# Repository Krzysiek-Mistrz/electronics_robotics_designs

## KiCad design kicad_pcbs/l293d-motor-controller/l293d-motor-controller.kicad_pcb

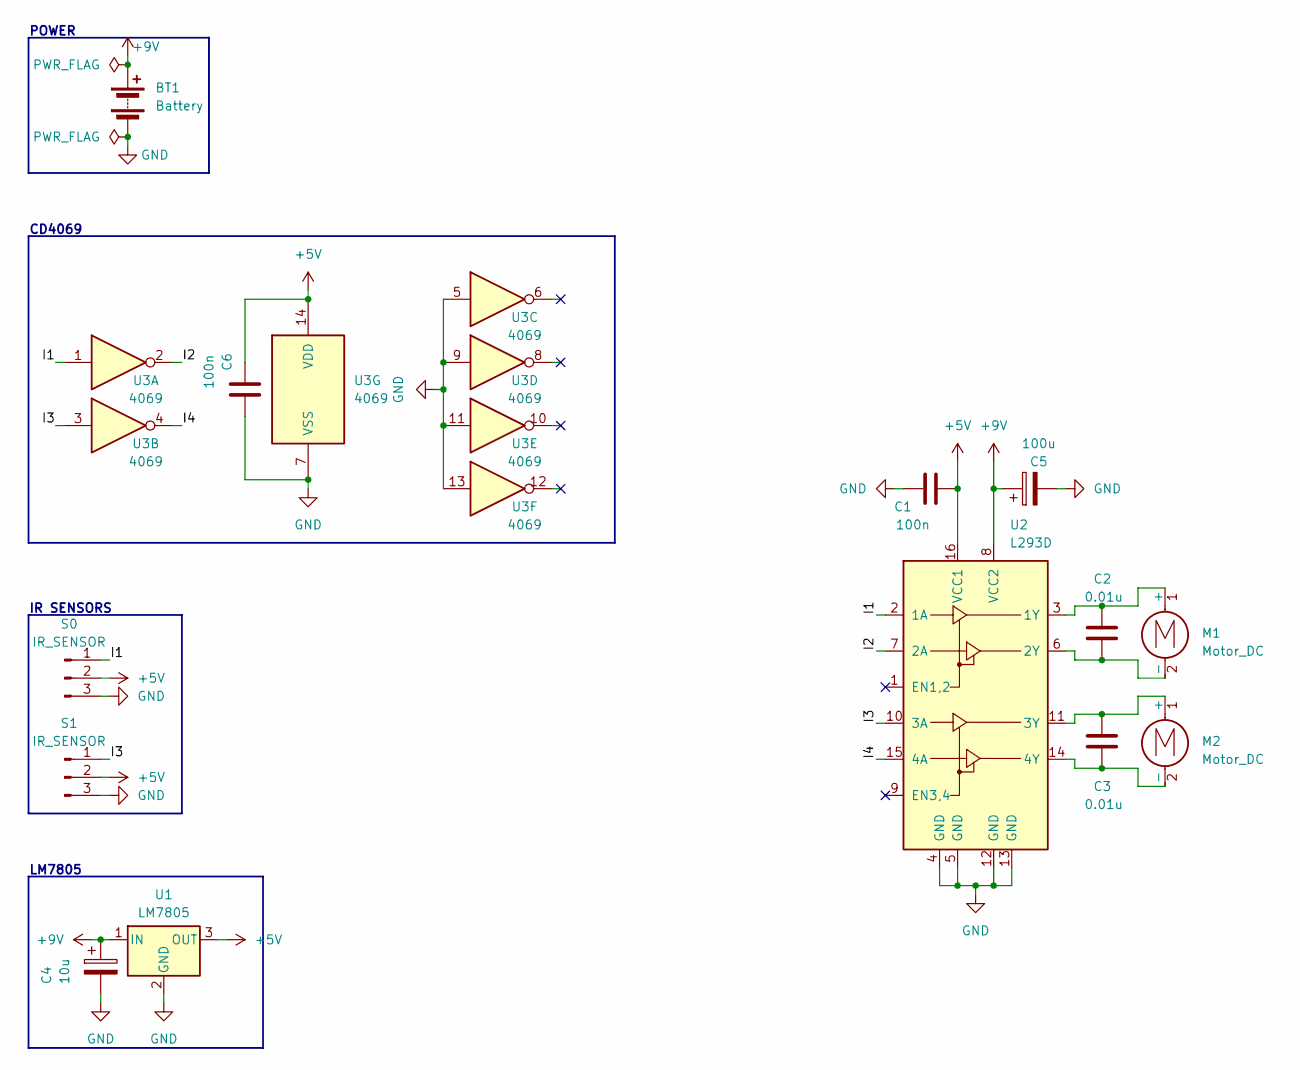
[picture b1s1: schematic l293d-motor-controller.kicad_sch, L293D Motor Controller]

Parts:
BT1: Battery; PinHeader_1x02_P2.54mm_Vertical
C1, C6: 100n; C_Disc_D3.0mm_W1.6mm_P2.50mm
C2, C3: 0.01u; C_Disc_D3.0mm_W1.6mm_P2.50mm
C4: 10u; CP_Radial_D4.0mm_P1.50mm
C5: 100u; CP_Radial_D4.0mm_P1.50mm
M1, M2: Motor_DC; PinHeader_1x02_P2.54mm_Vertical
S0, S1: IR_SENSOR; PinHeader_1x03_P2.54mm_Vertical
U1: LM7805; TO-220-3_Vertical
U2: L293D; DIP-16_W7.62mm
U3: 4069; DIP-14_W7.62mm

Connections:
+5V: C1.2, C6.1, S0.2, S1.2, U1.3 (OUT), U2.16 (VCC1), U3.14 (VDD)
+9V: BT1.1 (+), C4.1, C5.1, U1.1 (IN), U2.8 (VCC2)
/I1: S0.1, U2.2 (1A), U3.1
/I2: U2.7 (2A), U3.2
/I3: S1.1, U2.10 (3A), U3.3
/I4: U2.15 (4A), U3.4
GND: BT1.2 (-), C1.1, C4.2, C5.2, C6.2, S0.3, S1.3, U1.2 (GND), U2.4 (GND), U2.5 (GND), U2.12 (GND), U2.13 (GND), U3.5, U3.7 (VSS), U3.9, U3.11, U3.13
unnamed: C2.1, M1.1 (+), U2.3 (1Y)
unnamed: C2.2, M1.2 (-), U2.6 (2Y)
unnamed: C3.1, M2.1 (+), U2.11 (3Y)
unnamed: C3.2, M2.2 (-), U2.14 (4Y)

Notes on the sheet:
LM7805
POWER
IR SENSORS
CD4069

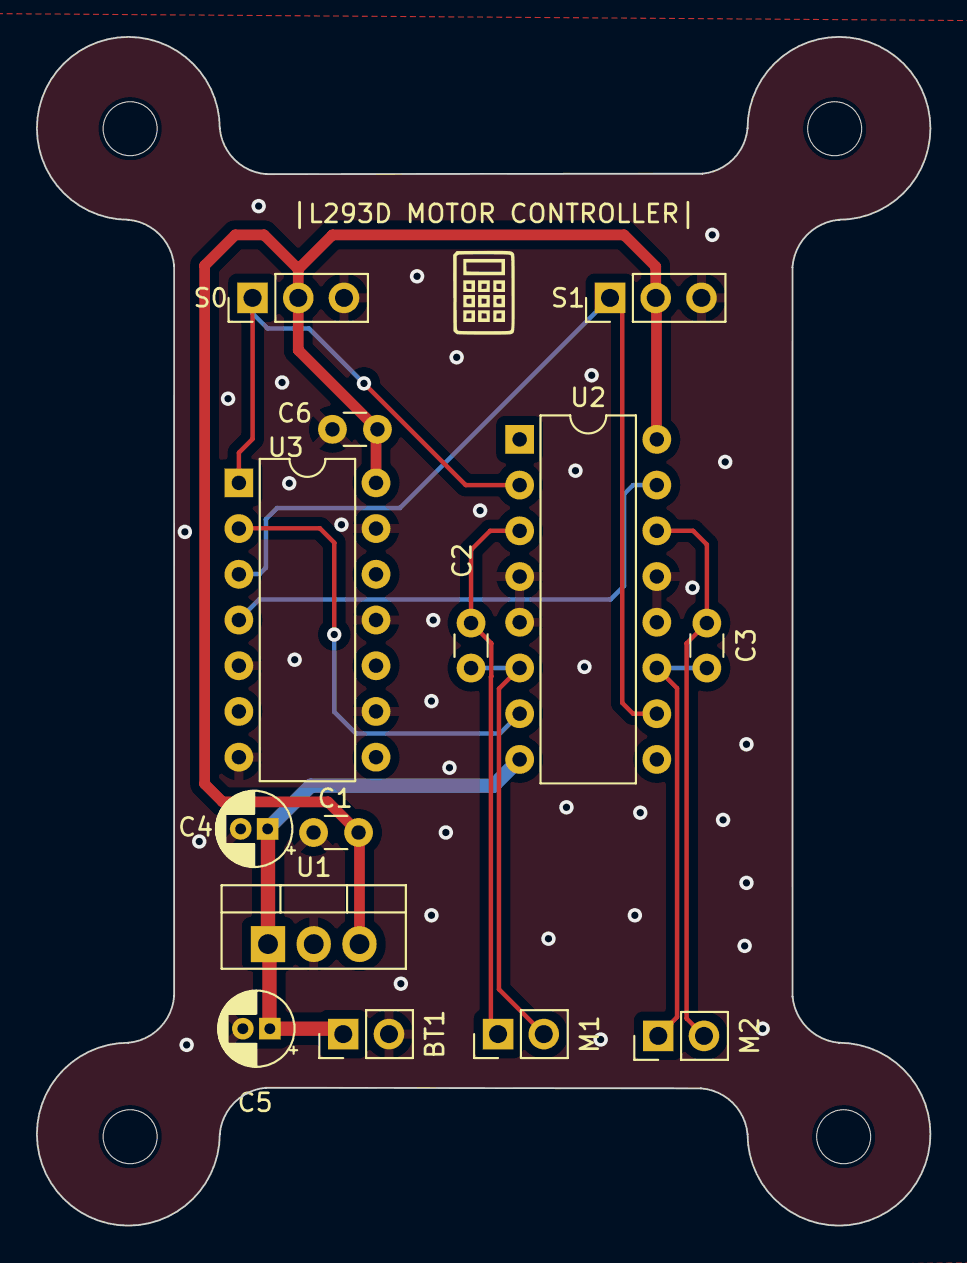
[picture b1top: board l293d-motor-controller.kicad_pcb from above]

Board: 2 copper layers, 49.6 x 66.0 mm, 14 parts (0 on the bottom side), 11 nets.

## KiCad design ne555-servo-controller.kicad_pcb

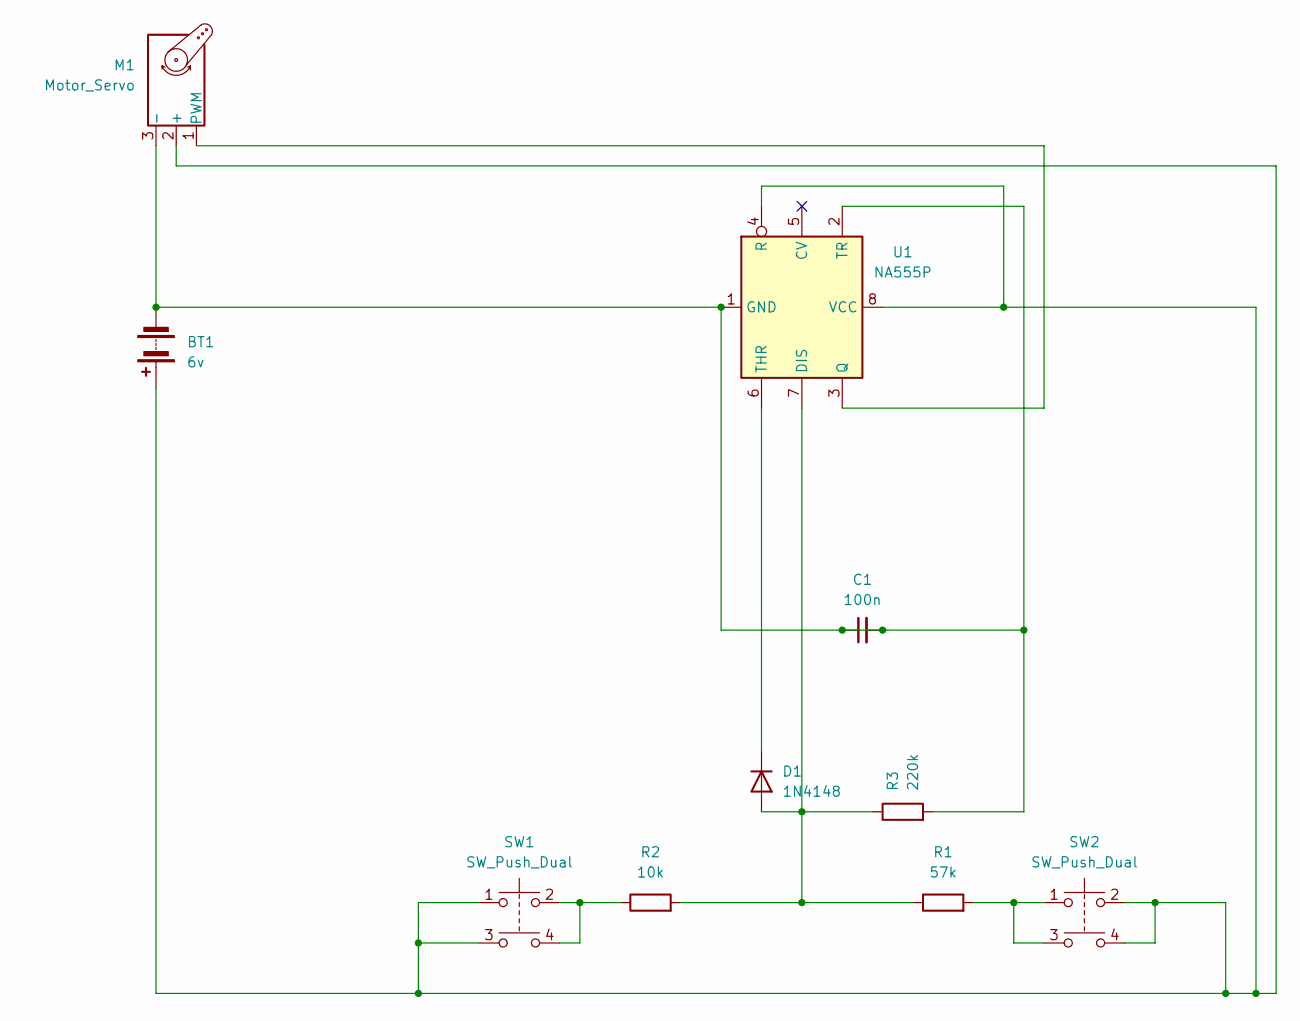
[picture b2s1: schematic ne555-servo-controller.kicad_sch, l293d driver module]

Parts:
BT1: 6v; PinHeader_2x01_P2.54mm_Vertical
C1: 100n; C_Disc_D3.4mm_W2.1mm_P2.50mm
D1: 1N4148; D_DO-35_SOD27_P7.62mm_Horizontal
M1: Motor_Servo; PinHeader_1x03_P2.54mm_Vertical
R1: 57k; R_Axial_DIN0207_L6.3mm_D2.5mm_P15.24mm_Horizontal
R2: 10k; R_Axial_DIN0207_L6.3mm_D2.5mm_P15.24mm_Horizontal
R3: 220k; R_Axial_DIN0207_L6.3mm_D2.5mm_P15.24mm_Horizontal
SW1, SW2: SW_Push_Dual; SW_Push_2P1T_Toggle_CK_PVA1xxH2xxxxxxV2
U1: NA555P; DIP-8_W7.62mm

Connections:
unnamed: BT1.1 (+), M1.2 (+), SW1.1, SW1.3, SW2.2, SW2.4, U1.4 (R), U1.8 (VCC)
unnamed: BT1.2 (-), C1.1, C1.2, M1.3 (-), R3.2, U1.1 (GND), U1.2 (TR)
unnamed: D1.2 (A), R1.1, R2.2, R3.1, U1.7 (DIS)
unnamed: D1.1 (K), U1.6 (THR)
unnamed: M1.1 (PWM), U1.3 (Q)
unnamed: R1.2, SW2.1, SW2.3
unnamed: R2.1, SW1.2, SW1.4

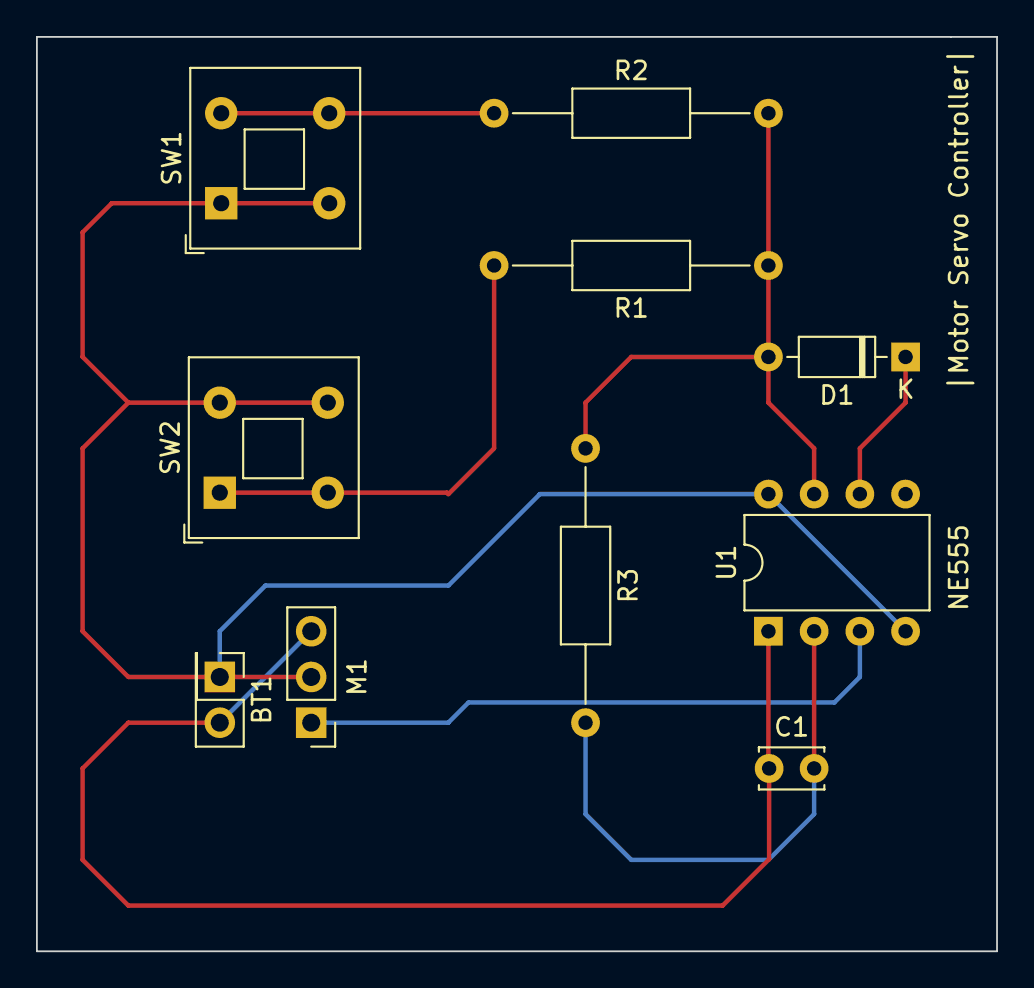
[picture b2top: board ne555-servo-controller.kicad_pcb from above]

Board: 2 copper layers, 53.3 x 50.8 mm, 10 parts (0 on the bottom side), 7 nets.
